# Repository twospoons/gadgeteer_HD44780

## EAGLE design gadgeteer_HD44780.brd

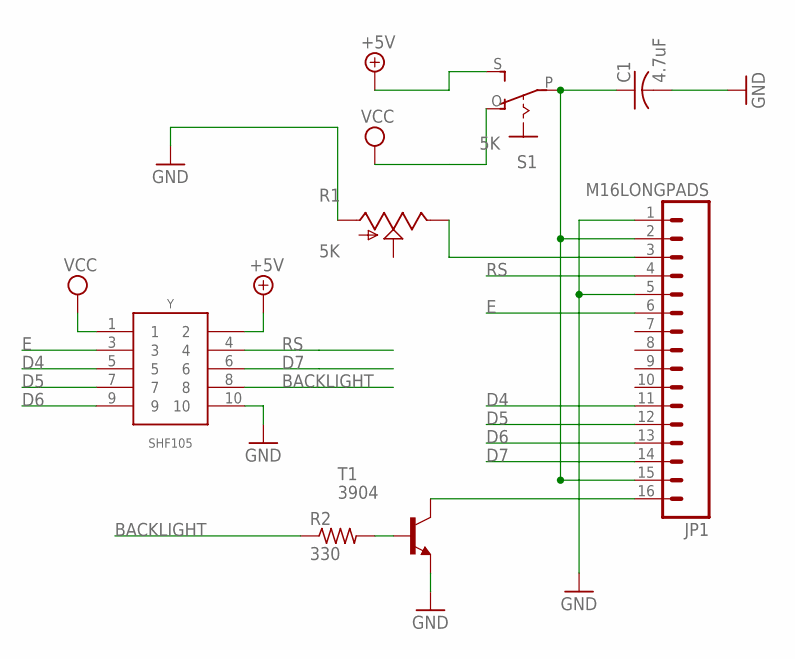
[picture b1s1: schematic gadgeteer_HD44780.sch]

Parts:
C1: 4.7uF; C1206K
JP1: M16LONGPADS; 1X16_LONGPADS
R1: 5K; BOURNS-TC33X
R2: 330; R0603
S1: 5K; EG1218
T1: 3904; SOT23-BEC
Y: SHF105; GAD_PAC_SMD

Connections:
+5V: S1.S, Y.2
BACKLIGHT: R2.1, Y.8
D4: JP1.11, Y.5
D5: JP1.12, Y.7
D6: JP1.13, Y.9
D7: JP1.14, Y.6
E: JP1.6, Y.3
GND: C1.2, JP1.1, JP1.5, R1.1 (A), T1.E, Y.10
unnamed: JP1.3, R1.3 (E)
unnamed: C1.1, JP1.2, JP1.15, S1.P
unnamed: R2.2, T1.B
unnamed: JP1.16, T1.C
RS: JP1.4, Y.4
VCC: S1.O, Y.1

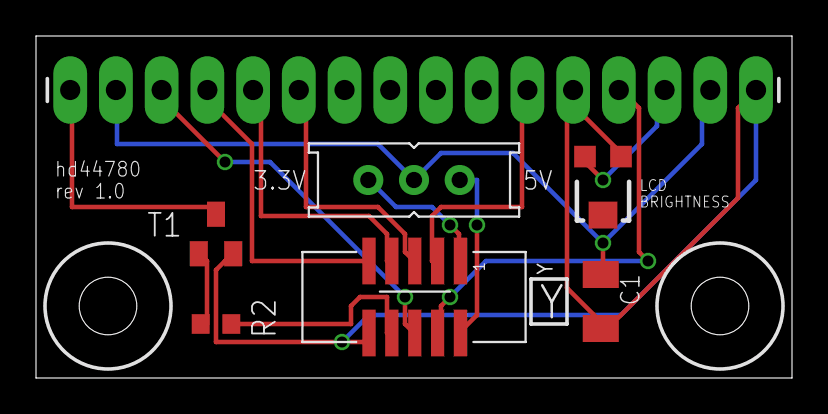
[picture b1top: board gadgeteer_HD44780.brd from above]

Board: 2 copper layers, 42.0 x 19.0 mm, 9 parts (0 on the bottom side), 14 nets.

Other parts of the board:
U$2, U$3: HOLE3.2

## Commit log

2012-10-22 Redesign of HD44780 display module. 3.3v and 5v tolerant with potmeter for brightness adjustment
2012-10-22 [FIX] Changed C1 to 1206K (Kemet) metric size
2012-10-23 mod epf

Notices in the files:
parts and their libraries:
SparkFun-Connectors: Licensing: CC v3.0 Share-Alike You are welcome to use this library for commercial purposes.
